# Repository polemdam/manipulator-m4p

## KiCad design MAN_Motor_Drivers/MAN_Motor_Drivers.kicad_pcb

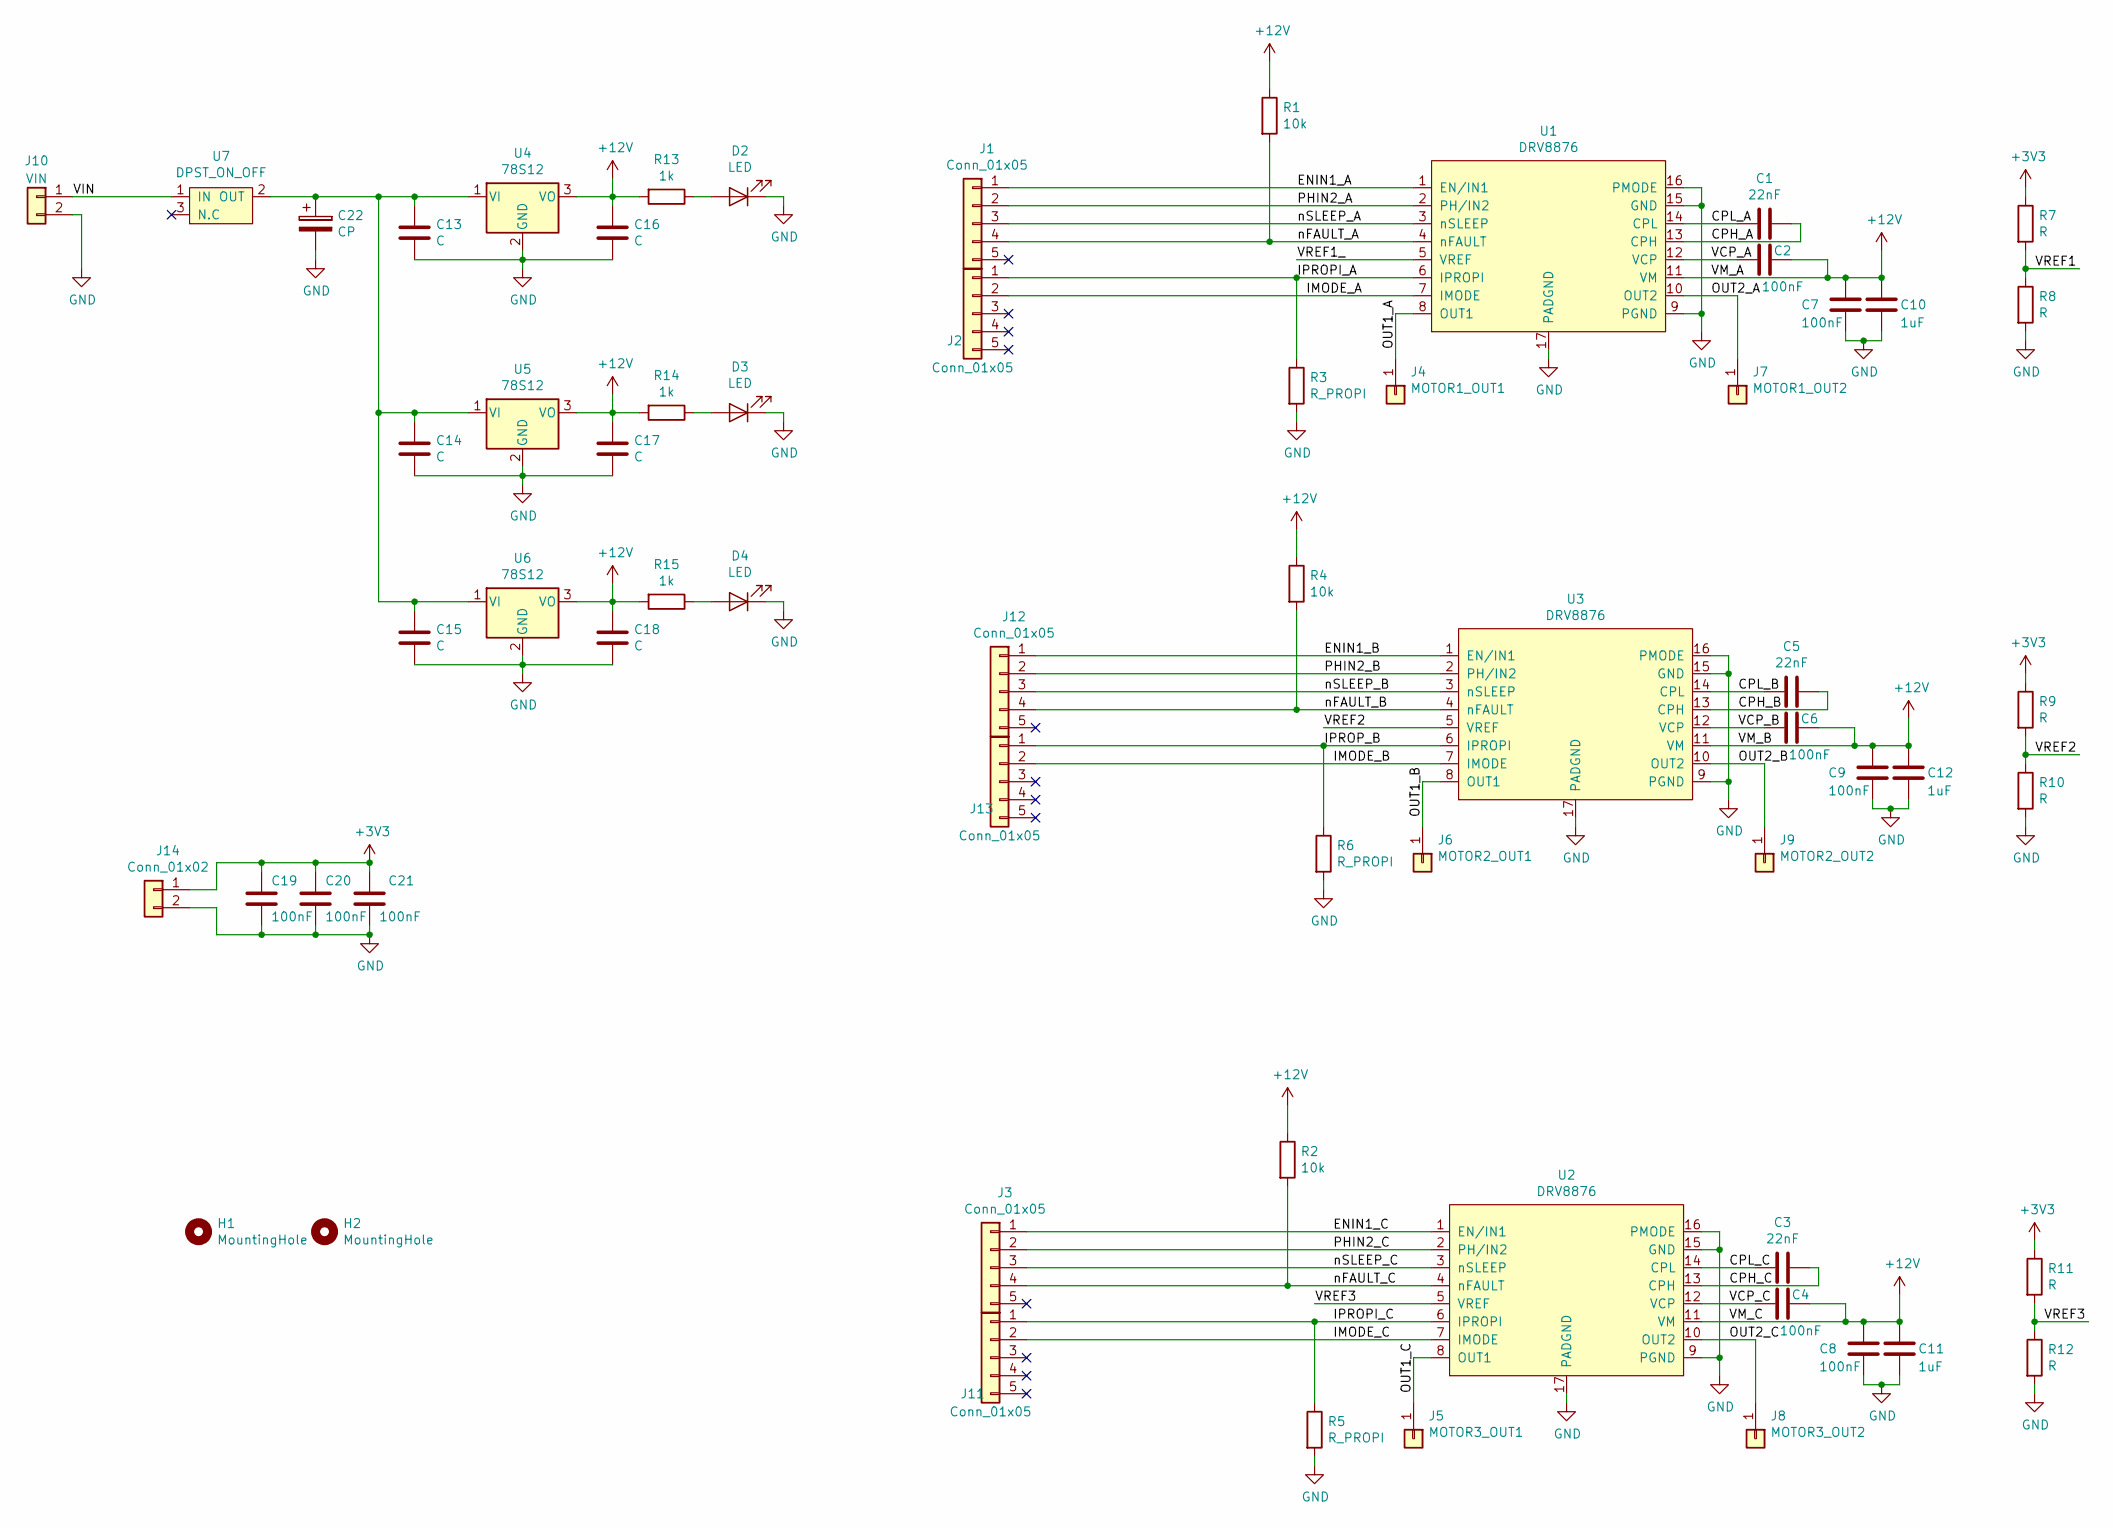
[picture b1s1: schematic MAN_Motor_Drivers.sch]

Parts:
C1, C3, C5: 22nF; C_0603_1608Metric_Pad1.05x0.95mm_HandSolder
C2, C4, C6, C7, C8, C9, C19, C20, C21: 100nF; C_0603_1608Metric_Pad1.05x0.95mm_HandSolder
C10, C11, C12: 1uF; C_0805_2012Metric_Pad1.15x1.40mm_HandSolder
C13, C14, C15, C16, C17, C18: C; C_0603_1608Metric_Pad1.05x0.95mm_HandSolder
C22: CP; CP_Elec_8x10
D2, D3, D4: LED; LED_0603_1608Metric_Pad1.05x0.95mm_HandSolder
H1, H2: MountingHole; MountingHole_2.7mm_M2.5
J1, J2, J3, J11, J12, J13: Conn_01x05; PinHeader_1x05_P2.54mm_Vertical
J4: MOTOR1_OUT1; Pin_D1.4mm_L8.5mm_W2.8mm_FlatFork
J5: MOTOR3_OUT1; Pin_D1.4mm_L8.5mm_W2.8mm_FlatFork
J6: MOTOR2_OUT1; Pin_D1.4mm_L8.5mm_W2.8mm_FlatFork
J7: MOTOR1_OUT2; Pin_D1.4mm_L8.5mm_W2.8mm_FlatFork
J8: MOTOR3_OUT2; Pin_D1.4mm_L8.5mm_W2.8mm_FlatFork
J9: MOTOR2_OUT2; Pin_D1.4mm_L8.5mm_W2.8mm_FlatFork
J10: VIN; SolderWirePad_1x02_P7.62mm_Drill2mm
J14: Conn_01x02; PinHeader_1x02_P2.54mm_Vertical
R1, R2, R4: 10k; R_0603_1608Metric_Pad1.05x0.95mm_HandSolder
R3, R5, R6: R_PROPI; R_0603_1608Metric_Pad1.05x0.95mm_HandSolder
R7, R8, R9, R10, R11, R12: R; R_0603_1608Metric_Pad1.05x0.95mm_HandSolder
R13, R14, R15: 1k; R_0603_1608Metric_Pad1.05x0.95mm_HandSolder
U1, U2, U3: DRV8876; HTSSOP-16-1EP_4.4x5mm_P0.65mm_EP3.4x5mm
U4, U5, U6: 78S12; TO-220-3_Vertical
U7: DPST_ON_OFF

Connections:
+3V3: C19.1, C20.1, C21.1, J14.1, R7.1, R9.1, R11.1
+12V: C2.1, C4.1, C6.1, C7.1, C8.1, C9.1, C10.1, C11.1, C12.1, C16.1, C17.1, C18.1, R1.1, R2.1, R4.1, R13.2, R14.2, R15.2, U1.11 (VM), U2.11 (VM), U3.11 (VM), U4.3 (VO), U5.3 (VO), U6.3 (VO)
/CPH_A: C1.1, U1.13 (CPH)
/CPH_B: C5.1, U3.13 (CPH)
/CPH_C: C3.1, U2.13 (CPH)
/CPL_A: C1.2, U1.14 (CPL)
/CPL_B: C5.2, U3.14 (CPL)
/CPL_C: C3.2, U2.14 (CPL)
/ENIN1_A: J1.1, U1.1 (EN/IN1)
/ENIN1_B: J12.1, U3.1 (EN/IN1)
/ENIN1_C: J3.1, U2.1 (EN/IN1)
/IMODE_A: J2.2, U1.7 (IMODE)
/IMODE_B: J13.2, U3.7 (IMODE)
/IMODE_C: J11.2, U2.7 (IMODE)
/IPROPI_A: J2.1, R3.1, U1.6 (IPROPI)
/IPROPI_C: J11.1, R5.1, U2.6 (IPROPI)
/IPROP_B: J13.1, R6.1, U3.6 (IPROPI)
/OUT1_A: J4.1, U1.8 (OUT1)
/OUT1_B: J6.1, U3.8 (OUT1)
/OUT1_C: J5.1, U2.8 (OUT1)
/OUT2_A: J7.1, U1.10 (OUT2)
/OUT2_B: J9.1, U3.10 (OUT2)
/OUT2_C: J8.1, U2.10 (OUT2)
/PHIN2_A: J1.2, U1.2 (PH/IN2)
/PHIN2_B: J12.2, U3.2 (PH/IN2)
/PHIN2_C: J3.2, U2.2 (PH/IN2)
/VCP_A: C2.2, U1.12 (VCP)
/VCP_B: C6.2, U3.12 (VCP)
/VCP_C: C4.2, U2.12 (VCP)
/VIN: J10.1, U7.1 (IN)
/VREF1: R7.2, R8.1
/VREF2: R9.2, R10.1, U3.5 (VREF)
/VREF3: R11.2, R12.1, U2.5 (VREF)
/nFAULT_A: J1.4, R1.2, U1.4 (nFAULT)
/nFAULT_B: J12.4, R4.2, U3.4 (nFAULT)
/nFAULT_C: J3.4, R2.2, U2.4 (nFAULT)
/nSLEEP_A: J1.3, U1.3 (nSLEEP)
/nSLEEP_B: J12.3, U3.3 (nSLEEP)
/nSLEEP_C: J3.3, U2.3 (nSLEEP)
GND: C7.2, C8.2, C9.2, C10.2, C11.2, C12.2, C13.2, C14.2, C15.2, C16.2, C17.2, C18.2, C19.2, C20.2, C21.2, C22.2, D2.1 (K), D3.1 (K), D4.1 (K), J10.2, J14.2, R3.2, R5.2, R6.2, R8.2, R10.2, R12.2, U1.9 (PGND), U1.15 (GND), U1.16 (PMODE), U1.17 (PADGND), U2.9 (PGND), U2.15 (GND), U2.16 (PMODE), U2.17 (PADGND), U3.9 (PGND), U3.15 (GND), U3.16 (PMODE), U3.17 (PADGND), U4.2 (GND), U5.2 (GND), U6.2 (GND)
unnamed: C13.1, C14.1, C15.1, C22.1, U4.1 (VI), U5.1 (VI), U6.1 (VI), U7.2 (OUT)
unnamed: D2.2 (A), R13.1
unnamed: D3.2 (A), R14.1
unnamed: D4.2 (A), R15.1

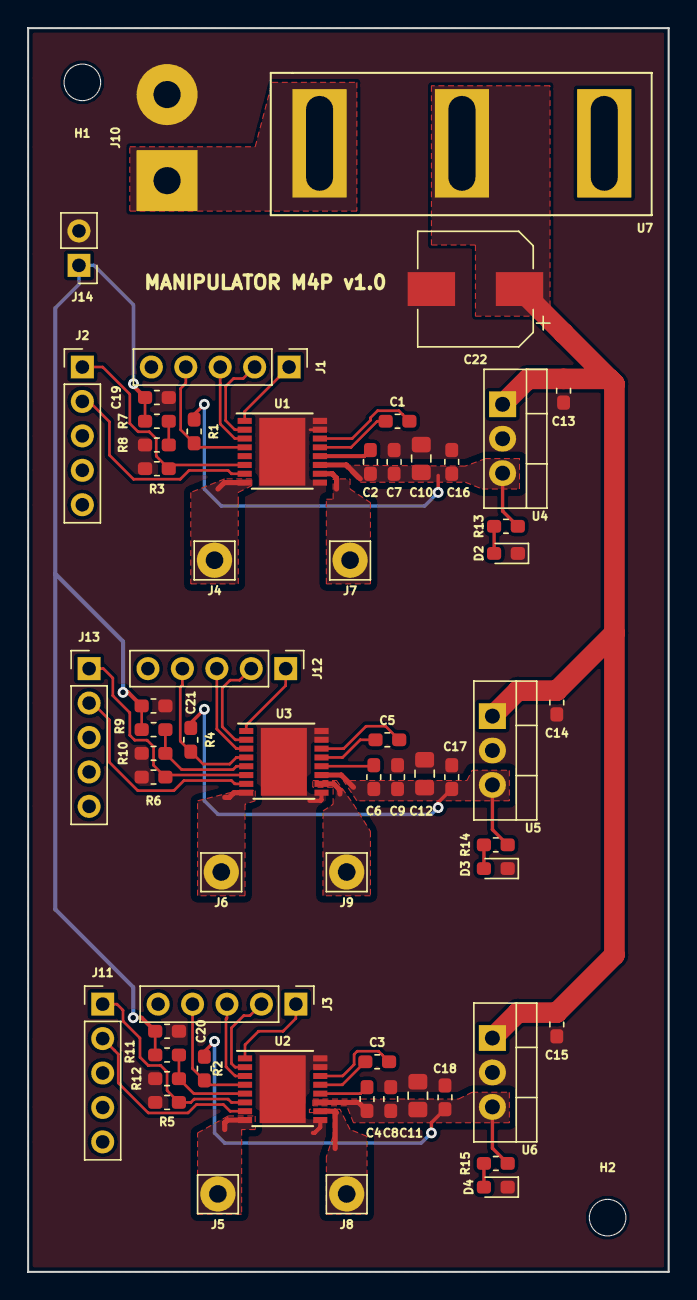
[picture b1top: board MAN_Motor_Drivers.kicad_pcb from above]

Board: 2 copper layers, 47.2 x 91.8 mm, 63 parts (0 on the bottom side), 44 nets.

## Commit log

2021-03-21 updated 3D model
2021-03-29 Matlab initialization commit
2021-04-02 layout finished
2021-04-02 brushed motors stucture
2021-04-06 zmiany dla manipulatora 3R
2021-04-21 Dodano fukncje obliczajace jakobian a.,PZK, OZK, macierz transformacji
2021-04-26 Aplikacja wstępna komunikacja
2021-04-26 Program na STM32 do testow
2021-04-26 Efekt dzialania aplikacji
2021-04-26 Ustawienia TIM oraz konf STM32
2021-06-04 current version
2021-06-06 added more advanced application
2021-06-06 added 3D model to application
2021-06-06 finsl dymbolic dynamic
2021-06-06 first symbolic dynamic
2021-06-06 very first version of algorithm function
2021-06-07 added communication with model 3D
2021-06-07 test program of control algorithm
2021-06-07 finish work on the application
2021-06-07 Add files via upload
    final version
